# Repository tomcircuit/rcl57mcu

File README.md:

# rcl57mcu

## MCU-based retrofit for TI-57 Programmable Calculators

This project came about because I stumbled across a TI-57 calculator with a "bad brain". The TMC1501 calculator-on-a-chip was faulty. This, in turn, led me to read more about this particular calculator and how the CPU inside functions. 

Fortunately, I am 'standing on the shoulders of giants' here - three people that have been of great help to me are Joerg Woerner, Jeff Parsons and Paul Novaes. All have humored me by answering my emails and helping me understand how the hardware works. 

Joerg's DATAMATH pages are amazing reading, and in particular there is an excellent [overview of the TMC1501 calculator-on-a-chip IC](http://www.datamath.org/Chips/TMC1500.htm) used in the TI-57.

Jeff Parsons' TI-57 pages include an online emulator and lots of history on TI-57 development. Extremely helpful is his [collection and analysis of original Texas Instruments patents](https://www.pcjs.org/machines/ti/ti57/patents/) filed around the introduction of this calculator.

Both Jeff and Paul have created TI-57 emulators. Paul's is an iOS app, and Jeff's is browser-based. Both emulate the TMC1501 CPU innards, which in turn execute the original TI-57 ROM code. So it is a faithful 'emulation'.

Paul was kind enough to put his [iOS app code](https://github.com/n3times/rcl57) up on GitHub

The 'guts' of the TMC1500 emulation are all contained within the 'engine' folder, and written in very generic and portable C. I learned an awful lot from studying this code.

## The Quest

I began to hatch a scheme - could I put a modern microcontroller (MCU) to the task of emulating the 1970's TMC1501? Could this hardware emulator be then installed into my defunct TI-57 to make it live again, perhaps even better than before?

See the hackaday page for more info on this project: 

https://hackaday.io/project/194963-ti-57-programmable-calculator-hardware-retrofit

Tom LeMense
February 2024

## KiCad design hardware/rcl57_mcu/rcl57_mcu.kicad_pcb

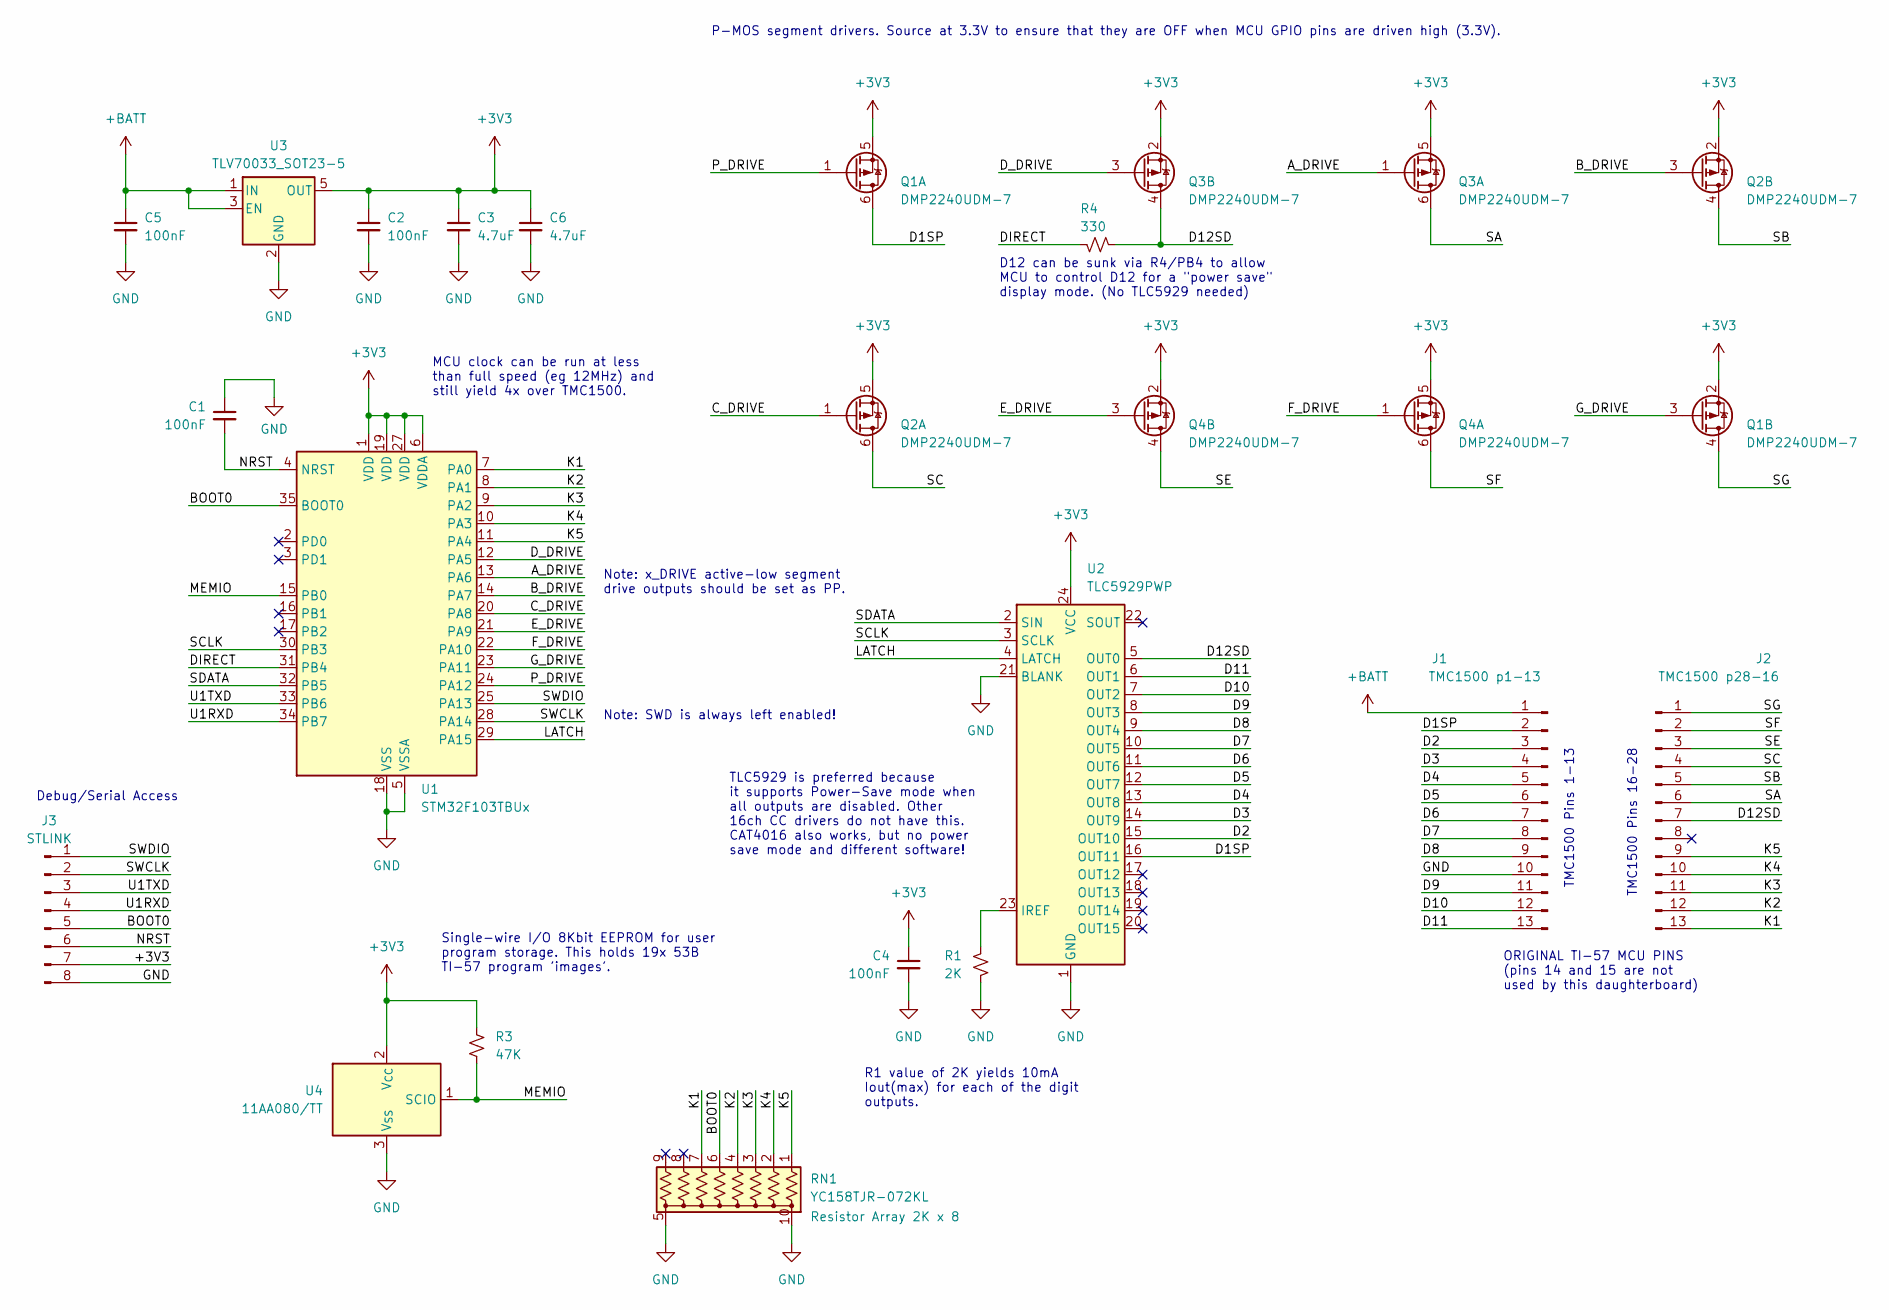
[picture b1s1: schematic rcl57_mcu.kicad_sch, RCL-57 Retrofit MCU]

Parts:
C1, C2, C4, C5: 100nF; C_0805_2012Metric
C3, C6: 4.7uF; C_0805_2012Metric
J1: TMC1500 p1-13; PinHeader_1x13_P2.54mm_Vertical
J2: TMC1500 p28-16; PinHeader_1x13_P2.54mm_Vertical
J3: STLINK; PinHeader_1x08_P2.00mm_Vertical
Q1, Q2, Q3, Q4: DMP2240UDM-7; SOT-23-6
R1: 2K; R_0805_2012Metric_Pad1.20x1.40mm_HandSolder
R3: 47K; R_0805_2012Metric_Pad1.20x1.40mm_HandSolder
R4: 330; R_0805_2012Metric_Pad1.20x1.40mm_HandSolder
RN1: YC158TJR-072KL; R_Array_Convex_5x0603
U1: STM32F103TBUx; QFN-36-1EP_6x6mm_P0.5mm_EP4.1x4.1mm
U2: TLC5929PWP; TSSOP-24-1EP_4.4x7.8mm_P0.65mm_EP3.2x5mm
U3: TLV70033_SOT23-5; SOT-23-5
U4: 11AA080/TT; SOT-23

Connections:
+3V3: C2.1, C3.1, C4.1, C6.1, J3.7, Q1.2 (SB), Q1.5 (SA), Q2.2 (SB), Q2.5 (SA), Q3.2 (SB), Q3.5 (SA), Q4.2 (SB), Q4.5 (SA), R3.1, U1.1 (VDD), U1.6 (VDDA), U1.19 (VDD), U1.27 (VDD), U2.24 (VCC), U3.5 (OUT), U4.2 (V_{CC})
+BATT: C5.1, J1.1, U3.1 (IN), U3.3 (EN)
/A_DRIVE: Q3.1 (GA), U1.13 (PA6)
/BOOT0: J3.5, RN1.6 (R5), U1.35 (BOOT0)
/B_DRIVE: Q2.3 (GB), U1.14 (PA7)
/C_DRIVE: Q2.1 (GA), U1.20 (PA8)
/D1SP: J1.2, Q1.6 (DA), U2.16 (OUT11)
/D2: J1.3, U2.15 (OUT10)
/D3: J1.4, U2.14 (OUT9)
/D4: J1.5, U2.13 (OUT8)
/D5: J1.6, U2.12 (OUT7)
/D6: J1.7, U2.11 (OUT6)
/D7: J1.8, U2.10 (OUT5)
/D8: J1.9, U2.9 (OUT4)
/D9: J1.11, U2.8 (OUT3)
/D10: J1.12, U2.7 (OUT2)
/D11: J1.13, U2.6 (OUT1)
/D12SD: J2.7, Q3.4 (DB), R4.1, U2.5 (OUT0)
/DIRECT: R4.2, U1.31 (PB4)
/D_DRIVE: Q3.3 (GB), U1.12 (PA5)
/E_DRIVE: Q4.3 (GB), U1.21 (PA9)
/F_DRIVE: Q4.1 (GA), U1.22 (PA10)
/G_DRIVE: Q1.3 (GB), U1.23 (PA11)
/K1: J2.13, RN1.7 (R6), U1.7 (PA0)
/K2: J2.12, RN1.4 (R4), U1.8 (PA1)
/K3: J2.11, RN1.3 (R3), U1.9 (PA2)
/K4: J2.10, RN1.2 (R2), U1.10 (PA3)
/K5: J2.9, RN1.1 (R1), U1.11 (PA4)
/LATCH: U1.29 (PA15), U2.4 (LATCH)
/MEMIO: R3.2, U1.15 (PB0), U4.1 (SCIO)
/NRST: C1.2, J3.6, U1.4 (NRST)
/P_DRIVE: Q1.1 (GA), U1.24 (PA12)
/SA: J2.6, Q3.6 (DA)
/SB: J2.5, Q2.4 (DB)
/SC: J2.4, Q2.6 (DA)
/SCLK: U1.30 (PB3), U2.3 (SCLK)
/SDATA: U1.32 (PB5), U2.2 (SIN)
/SE: J2.3, Q4.4 (DB)
/SF: J2.2, Q4.6 (DA)
/SG: J2.1, Q1.4 (DB)
/SWCLK: J3.2, U1.28 (PA14)
/SWDIO: J3.1, U1.25 (PA13)
/U1RXD: J3.4, U1.34 (PB7)
/U1TXD: J3.3, U1.33 (PB6)
GND: C1.1, C2.2, C3.2, C4.2, C5.2, C6.2, J1.10, J3.8, R1.2, RN1.5 (common1), RN1.10 (common2), U1.5 (VSSA), U1.18 (VSS), U1.26 (VSS), U1.36 (VSS), U1.37 (VSS), U2.1 (GND), U2.21 (BLANK), U2.25 (GND), U3.2 (GND), U3.4 (NC), U4.3 (V_{SS})
unnamed: R1.1, U2.23 (IREF)

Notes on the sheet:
TLC5929 is preferred because it supports Power-Save mode when all outputs are disabled. Other 16ch CC drivers do not have this. CAT4016 also works, but no power save mode and different software!
Single-wire I/O 8Kbit EEPROM for user program storage. This holds 19x 53B TI-57 program 'images'.
Note: SWD is always left enabled!
D12 can be sunk via R4/PB4 to allow MCU to control D12 for a "power save" display mode. (No TLC5929 needed)
TMC1500 Pins 1-13
ORIGINAL TI-57 MCU PINS (pins 14 and 15 are not used by this daughterboard)
P-MOS segment drivers. Source at 3.3V to ensure that they are OFF when MCU GPIO pins are driven high (3.3V).
R1 value of 2K yields 10mA Iout(max) for each of the digit outputs.
TMC1500 Pins 16-28
Debug/Serial Access
MCU clock can be run at less than full speed (eg 12MHz) and still yield 4x over TMC1500.
Note: x_DRIVE active-low segment drive outputs should be set as PP.

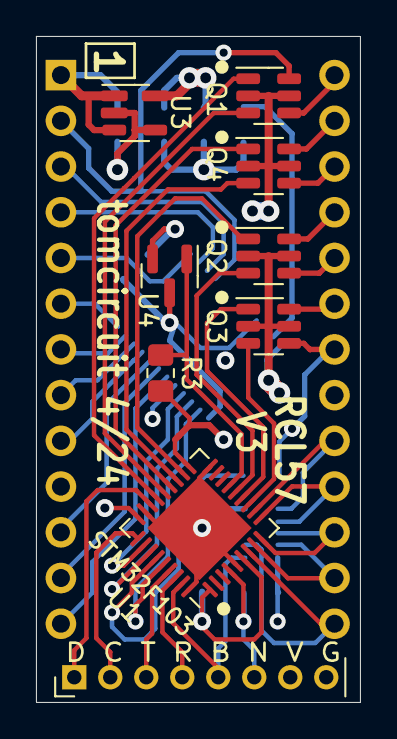
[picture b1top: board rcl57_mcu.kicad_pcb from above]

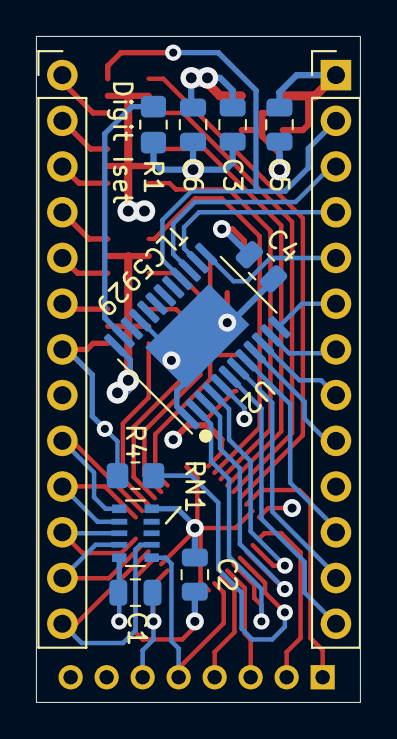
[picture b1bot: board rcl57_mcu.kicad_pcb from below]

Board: 4 copper layers, 18.0 x 37.0 mm, 21 parts (12 on the bottom side), 46 nets.

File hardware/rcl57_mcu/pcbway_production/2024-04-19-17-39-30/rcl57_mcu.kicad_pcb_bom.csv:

designator,quantity,value,pack,mpn,mount_type
"C1, C2, C4, C5",4,100nF,C_0805_2012Metric,,smt
"C3, C6",2,4.7uF,C_0805_2012Metric,,smt
J1,1,TMC1500 p1-13,PinHeader_1x13_P2.54mm_Vertical,,tht
J2,1,TMC1500 p28-16,PinHeader_1x13_P2.54mm_Vertical,,tht
J3,1,STLINK,PinHeader_1x08_P2.00mm_Vertical,,tht
"Q1, Q2, Q3, Q4",4,DMP2240UDM-7,SOT-23-6,,smt
R1,1,2K,R_0805_2012Metric_Pad1.20x1.40mm_HandSolder,,smt
R3,1,47K,R_0805_2012Metric_Pad1.20x1.40mm_HandSolder,,smt
R4,1,330,R_0805_2012Metric_Pad1.20x1.40mm_HandSolder,,smt
RN1,1,"YC158TJR-072KL
",R_Array_Convex_5x0603,,smt
U1,1,STM32F103TBUx,QFN-36-1EP_6x6mm_P0.5mm_EP4.1x4.1mm,,smt
U2,1,TLC5929PWP,TSSOP-24-1EP_4.4x7.8mm_P0.65mm_EP3.2x5mm,,smt
U3,1,TLV70033_SOT23-5,SOT-23-5,,smt
U4,1,11AA080/TT,SOT-23,,smt

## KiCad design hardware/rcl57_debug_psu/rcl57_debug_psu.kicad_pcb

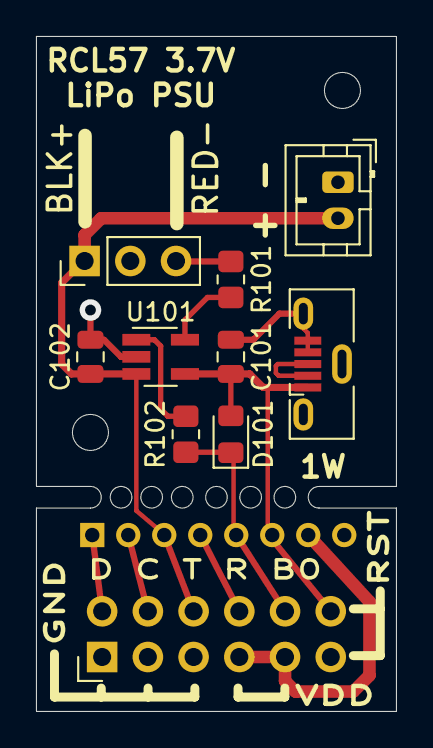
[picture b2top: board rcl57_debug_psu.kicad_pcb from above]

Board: 2 copper layers, 20.0 x 37.5 mm, 13 parts (1 on the bottom side), 15 nets.

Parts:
C101, C102: 4.7uF; C_0805_2012Metric
D101: LED; LED_0805_2012Metric_Pad1.15x1.40mm_HandSolder
H101, H102: MountingHole; MountingHole_2mm
J101: USB_Micro-B_Molex-105133-0001
J102: JST PH 2mm; JST_PH_B2B-PH-K_1x02_P2.00mm_Vertical
J103: CALC; PinHeader_1x03_P2.54mm_Vertical
J201: RCL57_BOARD; PinSocket_1x08_P2.00mm_Vertical
J202: DEBUG; PinHeader_2x06_P2.54mm_Vertical
R101: 4.7K; R_0805_2012Metric_Pad1.20x1.40mm_HandSolder
R102: 470; R_0805_2012Metric_Pad1.20x1.40mm_HandSolder
U101: MCP73831-2-OT; SOT-23-5_HandSoldering

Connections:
/RCL57 Retrofit - PSU Board/VBAT: C102.1, J102.2, J103.1, U101.3 (VBAT)
/RCL57 Retrofit - PSU Board/VUSB: C101.1, D101.2 (A), J101.1 (VBUS), U101.4 (VDD)
/RCL557 Retrofit - Debug Board/BOOT02: J201.5, J202.10
/RCL557 Retrofit - Debug Board/GND2: J201.8, J202.1, J202.3, J202.5, J202.11
/RCL557 Retrofit - Debug Board/NRST2: J201.6, J202.12
/RCL557 Retrofit - Debug Board/SWCLK12: J201.2, J202.4
/RCL557 Retrofit - Debug Board/SWDIO2: J201.1, J202.2
/RCL557 Retrofit - Debug Board/U1RXD2: J201.4, J202.8
/RCL557 Retrofit - Debug Board/U1TXD2: J201.3, J202.6
/RCL557 Retrofit - Debug Board/VDD2: J201.7, J202.7, J202.9
GND1: C101.2, C102.2, J101.4 (ID), J101.5 (GND), J101.6 (Shield), J102.1, J103.3, R101.2, U101.2 (VSS)
unnamed: D101.1 (K), R102.2
unnamed: J101.2 (D-), J101.3 (D+)
unnamed: R101.1, U101.5 (PROG)
unnamed: R102.1, U101.1 (STAT)

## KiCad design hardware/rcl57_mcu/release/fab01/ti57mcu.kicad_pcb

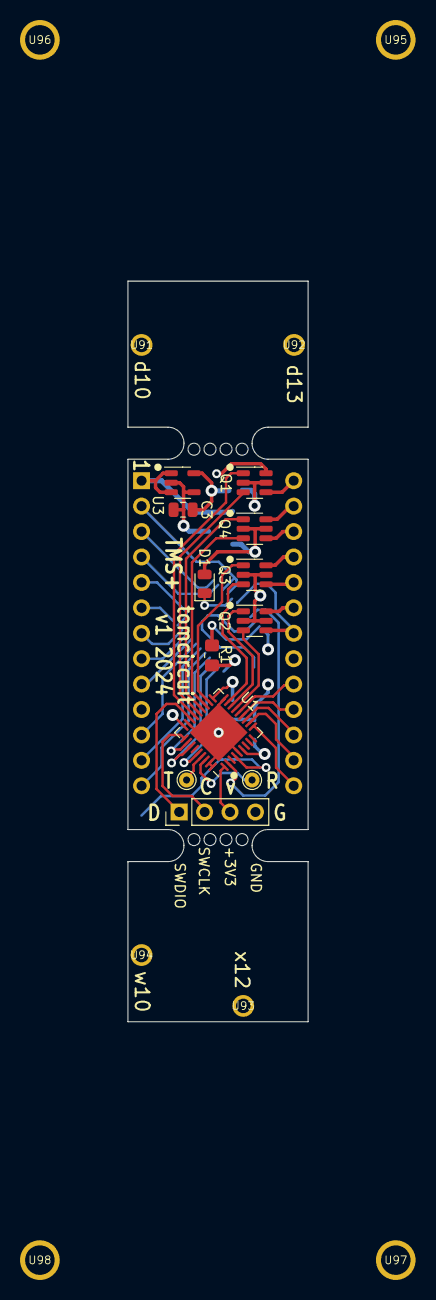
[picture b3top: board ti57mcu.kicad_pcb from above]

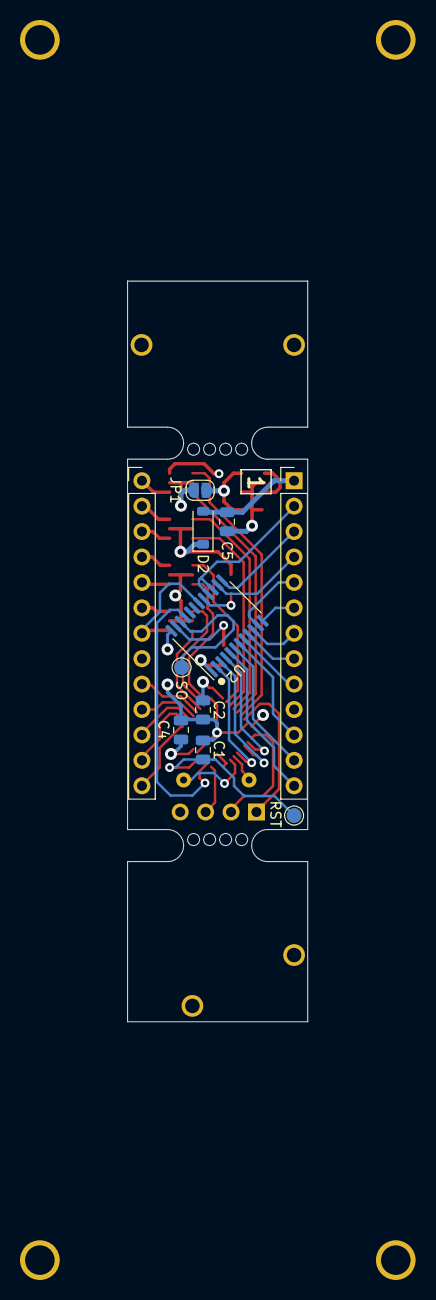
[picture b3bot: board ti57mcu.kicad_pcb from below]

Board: 4 copper layers, 18.0 x 74.0 mm, 32 parts (11 on the bottom side), 47 nets.

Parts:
C1, C2, C4, C5: 100nF; C_0805_2012Metric
C3: 4.7uF; C_0805_2012Metric
D1: LED; LED_0805_2012Metric
D2: MBR0520; D_SOD-123
J1: TMS1500 p1-14; PinHeader_1x13_P2.54mm_Vertical
J2: TMS1500 p28-15; PinHeader_1x13_P2.54mm_Vertical
J3: STLINK; PinHeader_1x04_P2.54mm_Vertical
JP1: REGLED; SolderJumper-2_P1.3mm_Open_RoundedPad1.0x1.5mm
Q1, Q2, Q3, Q4: DMP2240UDM-7; SOT-23-6
R1: 6.8K; R_0805_2012Metric_Pad1.20x1.40mm_HandSolder
TP1: NRST; TestPoint_Pad_D1.5mm
TP2: SOUT; TestPoint_Pad_D1.5mm
TP7: TXD; TestPoint_THTPad_D1.5mm_Drill0.7mm
TP8: TEST; TestPoint_THTPad_D1.5mm_Drill0.7mm
U1: STM32F103TBUx; QFN-36-1EP_6x6mm_P0.5mm_EP4.1x4.1mm
U2: CAT4016TY; TSSOP-24_4.4x7.8mm_P0.65mm
U3: TLV70033_SOT23-5; SOT-23-5
U91, U92, U93, U94: PIN_SMALL_SINGLE_DEVICE; PIN_SMALL_SINGLE
U95, U96, U97, U98: PIN_LARGE_SINGLE_DEVICE; PIN_LARGE_SINGLE_NOSILK
U99: GUIDE_10X10; BOARD_10X10_USERCMTS

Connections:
+3V3: C2.1, C3.1, C4.1, J3.3, JP1.2 (B), U1.1 (VDD), U1.6 (VDDA), U1.19 (VDD), U1.27 (VDD), U2.24 (VDD), U3.5 (OUT)
+BATT: C5.1, D2.2 (A), J1.1, U3.1 (IN), U3.3 (EN)
/A_DRIVE: Q2.1 (GA), U1.16 (PB1)
/BLANK: U1.2 (PD0), U2.21 (BLANK)
/B_DRIVE: Q3.3 (GB), U1.17 (PB2)
/C_DRIVE: Q3.1 (GA), U1.20 (PA8)
/D1SP: J1.2, Q1.6 (DA), U2.15 (LED11), U2.16 (LED12)
/D2: J1.3, U2.13 (LED9)
/D3: J1.4, U2.14 (LED10)
/D4: J1.5, U2.11 (LED7)
/D5: J1.6, U2.12 (LED8)
/D6: J1.7, U2.10 (LED6)
/D7: J1.8, U2.9 (LED5)
/D8: J1.9, U2.8 (LED4)
/D9: J1.11, U2.7 (LED3)
/D10: J1.12, U2.6 (LED2)
/D11: J1.13, U2.5 (LED1)
/D12SD: J2.7, Q2.4 (DB), U2.18 (LED14)
/D_DRIVE: Q2.3 (GB), U1.15 (PB0)
/E_DRIVE: Q4.3 (GB), U1.21 (PA9)
/F_DRIVE: Q4.1 (GA), U1.22 (PA10)
/G_DRIVE: Q1.3 (GB), U1.23 (PA11)
/K1: J2.13, U1.10 (PA3)
/K2: J2.12, U1.11 (PA4)
/K3: J2.11, U1.12 (PA5)
/K4: J2.10, U1.13 (PA6)
/K5: J2.9, U1.14 (PA7)
/LATCH: U1.29 (PA15), U2.4 (LATCH)
/NRST: C1.2, TP1.1, U1.4 (NRST)
/P_DRIVE: Q1.1 (GA), U1.24 (PA12)
/S1CLK: U1.30 (PB3), U2.3 (CLK)
/S1MOSI: U1.32 (PB5), U2.2 (SIN)
/SA: J2.6, Q2.6 (DA)
/SB: J2.5, Q3.4 (DB)
/SC: J2.4, Q3.6 (DA)
/SE: J2.3, Q4.4 (DB)
/SF: J2.2, Q4.6 (DA)
/SG: J2.1, Q1.4 (DB)
/SOUT: TP2.1, U2.22 (SOUT)
/SWCLK: J3.2, U1.28 (PA14)
/SWDIO: J3.1, U1.25 (PA13)
/TEST: TP8.1, U1.34 (PB7)
/U1TXD: TP7.1, U1.33 (PB6)
GND: C1.1, C2.2, C3.2, C4.2, C5.2, J1.10, J3.4, R1.2, U1.5 (VSSA), U1.18 (VSS), U1.26 (VSS), U1.35 (BOOT0), U1.36 (VSS), U1.37 (VSS), U2.1 (GND), U3.2 (GND), U3.4 (NC)
unnamed: D1.1 (K), U2.17 (LED13)
unnamed: R1.1, U2.23 (RSET)
VBUS: D1.2 (A), D2.1 (K), JP1.1 (A), Q1.2 (SB), Q1.5 (SA), Q2.2 (SB), Q2.5 (SA), Q3.2 (SB), Q3.5 (SA), Q4.2 (SB), Q4.5 (SA)

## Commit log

2024-02-24 Initial commit
    fab01 KiCAD project
    rcl57console Pelles-C
    rcl57mcu Keil uVision
2024-02-24 HaD link, media files
    Updated readme with hackaday link, and added TI-57 image (from UK Computing History museum website) as well as 3D image from KiCAD fab01 release.
2024-02-28 checkin of V2 MCU board and V1 PSU/debug board
    these were split into two KiCad projects because the PSU and debug adapter only need 2 layers. Cleanup of KiCad projects, generation of PCB checkplots and schematic and assembly files.
2024-03-11 debug level software
    most hardware specific items are in mux57.c file, as display and keyboard support is the bulk of the embedded hardware task. license file updated to include Jeff Parsons' original MIT as well as MIT 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
2024-03-12 updated README and LICENSE files
    corrected attribution in the README.md files, and corrected the license scope.
2024-03-12 More attribution
    Attributed Joerg Woerner of DATAMATH as well.
2024-03-12 Update README.md
    cleaned up links, more attribution
2024-03-15 EEPROM support & powersave
    Testing of power-save feature, and initial EEPROM driver implemented. Still not ready to run on real hardware yet.
2024-03-15 Reduced CPU clock to 24 MHz
    Reduced CPU clock from 36MHz to 24MHz. This turned out to be a lot easier to do than I expected, and no ill effect upon program timing was observed.
2024-04-24 working on TI55 donor board
    ADC key column read, UNIO EEPROM read/init, power-save mode. Assumes V2 PCB with 2K pulldowns on K1-K5 inputs.
    Updated schematic and PCB to "v3" to include the pulldown pack and simplify power options. V3 board not yet sent out for fabrication.
2024-05-14 3D printed lid added
    version 1.3 of the 3D printed lid fits nicely into my TI-55 and TI-57 calculators. Design tool is OpenSCAD, so it would be easy to modify for other PCB e.g. one that makes 9V output for unmodified ca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
